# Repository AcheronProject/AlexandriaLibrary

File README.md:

# The Acheron Alexandria Library 

## Introduction

The Alexandria Library is a group of libraries aimed at electronic design; most libraries focus on KiCAD footprints, but some also contain KiCAD symbol libraries, some contain graphics and some contain STEP/3D model files.

## List of libraries:

### General use

- [**Acheron Symbols**](https://github.com/AcheronProject/acheron_Symbols): KiCAD symbol library;
- [**Acheron Components**](https://github.com/AcheronProject/acheron_Symbols): KiCAD footprint library for general components like integrated circuits, resistors, capacitors, LEDs, inductors, fuses *et cetera*;
- [**Acheron Hardware**](https://github.com/AcheronProject/acheron_Hardware.pretty): KiCAD footprint library for overall interaction hardware like standoffs, encoders, featherboards (Pro Micro, Blue Pill, Black Pill *et cetera*), buttons, battery holders, mounting screws;
- [**Acheron Graphics**](https://github.com/AcheronProject/acheron_Graphics.pretty): KiCAD footprint library for logos, flags, pretty graphics;
- [**Acheron 3D**](https://github.com/AcheronProject/acheron_3D): repository of 3D models used by the footprint libraries;

### Keyboard switch footprints

The libraries listed below are KiCAD footprint libraries for mechanical keyboard switches:

- [**Acheron MX**](https://github.com/AcheronProject/acheron_MX.pretty): exclusive support for MX-type switches;
- [**Acheron MX "Soldermask"**](https://github.com/AcheronProject/acheron_MX_soldermask.pretty): exclusive support for MX-type switches with the frontal pads covered in soldermask, hiding the pads in the front while exposing them on the back for soldering, for aesthetic purposes;
- [**Acheron MXH**](https://github.com/AcheronProject/acheron_MXH.pretty): exclusive support for MX-type switches using Kailh "hotswap" sockets;
- [**Acheron MXH "Metal Rings"**](https://github.com/AcheronProject/acheron_MXH_metalrings.pretty): exclusive support for MX-type switches using Kailh "hotswap" sockets with metallic rings around the switch contacts for aesthetic effect;
- [**Acheron MXA**](https://github.com/AcheronProject/acheron_MXA.pretty): hybrid MX-ALPS footprints;
- [**Acheron EC**](https://github.com/AcheronProject/acheron_EC.pretty): exclusive support for electrocapacitive ("Topre-style") switches;

### Macros, makefiles
- [**Acheron Setup**](https://github.com/AcheronProject/AcheronSetup): makefiles and bash scripts to automate some of the work needed to use and maintain a project based on the Acheron Library

### LTSPICE

- [**Acheron LTSPICE**](https://github.com/AcheronProject/acheron_ltspice): symbols and models for the LTSpice simulation software
- [**LT2PY**](https://github.com/Gondolindrim/lt2py): Python tool that converts data plots taken from LTSpice into Python plots, allowing to manipulate and edit the graphs

## Miscellaneous
- [**Acheron Ruler**](https://github.com/AcheronProject/AcheronRuler): in true greek geometry fashion, a ruler featuring both milimeter and inch measurements with electronic components footprints on the back;

## Showing support

Designs using the Alexandria Library into their composition can show support through the KiCAD footprints in the ``./alexandria_kicad_logos'' repository.

## Licensing

Each component of the Alexandria Library is subject to its own licensing and thorough reading is highly advised. This repository itself is licensed under a BSD-3 clause.

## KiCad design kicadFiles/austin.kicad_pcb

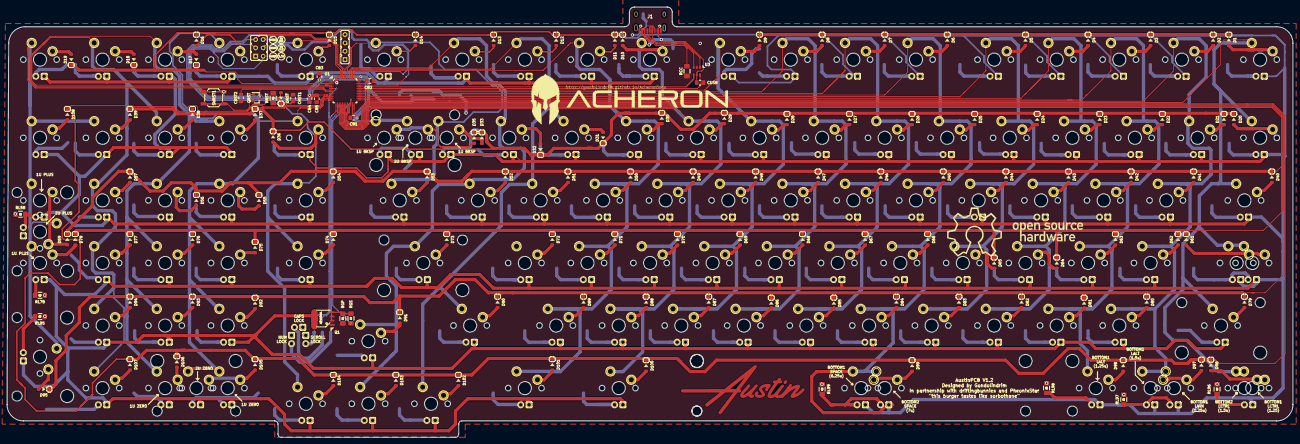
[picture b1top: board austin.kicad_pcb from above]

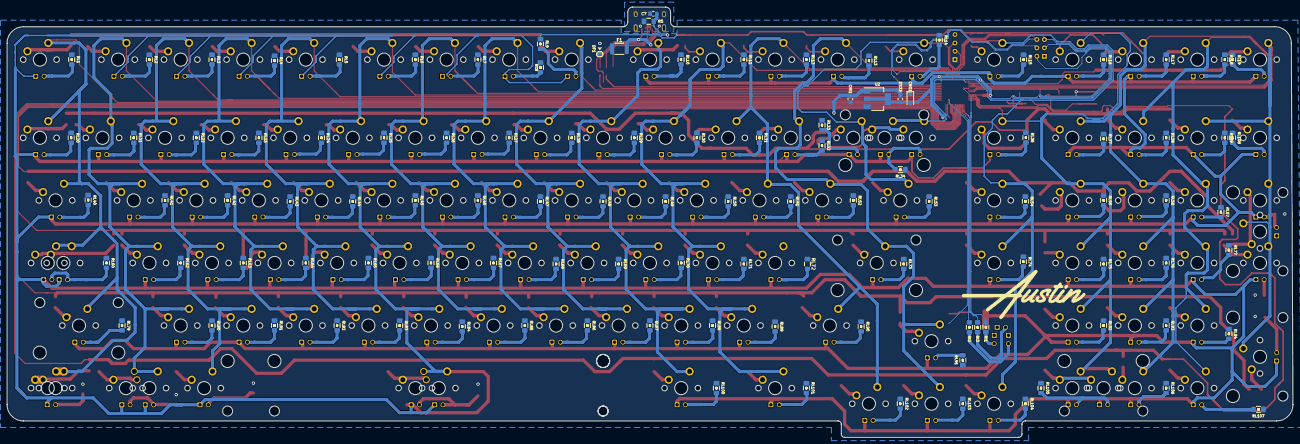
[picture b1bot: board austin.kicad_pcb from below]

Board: 2 copper layers, 391.5 x 131.0 mm, 472 parts (110 on the bottom side), 261 nets.

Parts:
C7: 4.7n; C_0805_2012Metric_Pad1.15x1.40mm_HandSolder
CB1, CB2, CB3, CB4: 100n; C_0805_2012Metric_Pad1.15x1.40mm_HandSolder
CB5: 10u; C_0805_2012Metric_Pad1.15x1.40mm_HandSolder
CRI1: 100n; C_0805_2012Metric_Pad1.15x1.40mm_HandSolder
CRO1: 100n; C_0805_2012Metric_Pad1.15x1.40mm_HandSolder
CRST1: 10u; C_0805_2012Metric_Pad1.15x1.40mm_HandSolder
CRST2: 4.7n; C_0805_2012Metric_Pad1.15x1.40mm_HandSolder
CUSB: 4.7n; C_0805_2012Metric_Pad1.15x1.40mm_HandSolder
D1, D2, D3, D4, D5, D6, D7, D8, D9, D10, D11, D12, D13, D14, D15, D16, D17, D18, D19, D20, D21, D22, D23, D24, D25, D26, D27, D28, D29, D30, D31, D32, D33, D35, D36, D37, D38, D39, D40, D41, D42, D43, D44, D45, D46, D47, D48, D49, D50, D51, D52, D53, D54, D55, D56, D57, D59, D61, D62, D63, D64, D65, D66, D67, D68, D69, D70, D71, D72, D73, D74, D75, D76, D77, D78, D79, D80, D81, D82, D83, D84, D85, D86, D87, D88, D89, D90, D91, D92, D93, D94, D95, D96, D97, D98, D99, D100, D101, D102, D103, D104, D105, D106, D107, D108: 1N4148; D_SOD-123
DF1: RB060M-60TR; D_SOD-123
DRST: 1N4148; D_SOD-123
DS33: 1N4007; D_SOD-123F
F1: 1A; Fuse_1812_4532Metric_Pad1.30x3.40mm_HandSolder
J1: TYPE-C-31-M12_13; TYPE-C-31-M-12
J2: Conn_01x04_Male; 4pinHeader
J5: Conn_01x06_Male; 6pinHeader
L1: Logo; austinLogo_16x40_Plated
L1#2: Logo; austinLogoSmall
L2: LogoBack; acheronLongExtended
L3: OSHLogo; osh-logoExtended
LED1, LED2, LED3, LED4, LED5, LED6, LED7, LED8, LED9, LED10, LED11, LED12, LED13, LED14, LED15, LED16, LED17, LED18, LED19, LED20, LED21, LED22, LED23, LED24, LED25, LED26, LED27, LED28, LED29, LED30, LED31, LED32, LED33, LED34, LED35, LED36, LED37, LED38, LED39, LED40, LED41, LED42, LED43, LED44, LED45, LED46, LED47, LED48, LED49, LED50, LED51, LED52, LED53, LED54, LED55, LED56, LED57, LED58, LED59, LED60, LED61, LED62, LED63, LED64, LED65, LED66, LED67, LED68, LED69, LED70, LED71, LED72, LED73, LED74, LED75, LED76, LED77, LED78, LED79, LED80, LED81, LED82, LED83, LED84, LED85, LED86, LED87, LED88, LED89, LED90, LED91, LED92, LED93, LED94, LED95, LED97, LED98, LED99, LED100, LED101, LED102, LED103, LED104, LED105, LED106, LED107, LED108, LED109, LED110, LED111, LED112: LED; thtLED
LEDCAPS1: LED; thtLED
LEDNUM1: LED; thtLED
LEDSCRL1: LED; thtLED
Q1: AO4406AL
QRST: DTC123J; SOT-23
R5: 1M; R_1206_3216Metric_Pad1.42x1.75mm_HandSolder
RCC: 5.1k; R_1206_3216Metric_Pad1.42x1.75mm_HandSolder
RGP: 10k; R_1026
RGS: 100; R_1026
RI1, RI2, RI3: 360; R_1026
RL1, RL2, RL3, RL4, RL5, RL6, RL7, RL8, RL9, RL10, RL11, RL12, RL13, RL14, RL15, RL16, RL17, RL18, RL19, RL20, RL21, RL22, RL23, RL24, RL25, RL26, RL27, RL28, RL29, RL30, RL31, RL32, RL33, RL34, RL36, RL37, RL38, RL39, RL40, RL41, RL42, RL43, RL44, RL45, RL46, RL47, RL48, RL49, RL50, RL51, RL52, RL53, RL54, RL55, RL56, RL57, RL58, RL60, RL62, RL63, RL64, RL65, RL66, RL67, RL68, RL69, RL70, RL71, RL73, RL74, RL75, RL76, RL77, RL78, RL79, RL80, RL81, RL82, RL83, RL84, RL85, RL86, RL87, RL88, RL89, RL90, RL91, RL92, RL93, RL94, RL95, RL96, RL97, RL98, RL99, RL100, RL101, RL102, RL103, RL104, RL105, RL106, RL107, RL108: 360; R_1026
RL72: 360; R_1206_3216Metric_Pad1.42x1.75mm_HandSolder
RRST: 100k; R_1026
SW1, SW2, SW3, SW4, SW5, SW6, SW7, SW8, SW9, SW10, SW11, SW12, SW13, SW14, SW15, SW16, SW17, SW18, SW19, SW20, SW21, SW22, SW23, SW24, SW25, SW26, SW27, SW28, SW29, SW30, SW31, SW32, SW33, SW35, SW36, SW37, SW38, SW39, SW41, SW42, SW43, SW44, SW45, SW46, SW47, SW48, SW49, SW50, SW51, SW52, SW54, SW55, SW56, SW57, SW58, SW62, SW63, SW64, SW65, SW66, SW67, SW68, SW69, SW70, SW71, SW72, SW74, SW75, SW76, SW77, SW78, SW80, SW81, SW82, SW83, SW84, SW85, SW86, SW87, SW88, SW89, SW91, SW92, SW93, SW94, SW102, SW103, SW104, SW105, SW106, SW107, SW108: MXSwitch; MX100
SW34: MXSwitch; MX200
SW40, SW53, SW100, SW101, SW109, SW110: MXSwitch; MX150
SW59, SW95, SW112: MXSwitch; MX200R
SW60, SW90: MXSwitch; MX175
SW61, SW96, SW97, SW98: MXSwitch; MX125
SW73, SW79: MXSwitch; MX225
SW99: MXSwitch; MX625R
SW111: MXSwitch; MX700R
SWRST1: SW_Push; smdPushBtn
U1: STM32F072_LQFP48; LQFP-48_7x7mm_P0.5mm
U2: TLV1117-33; SOT-223-3_TabPin2
U3: USBLC6-2SC6; SOT-23-6

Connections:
3.3V: CB1.1, CB2.1, CB3.1, CB4.1, CB5.1, CRO1.2, DS33.2, J5.6, SWRST1.1, U1.1, U1.9, U1.24, U1.36, U1.48, U2.2
5V: CRI1.2, DF1.1, DS33.1, F1.1, J2.1, RL1.1, RL2.1, RL3.1, RL4.1, RL5.1, RL6.1, RL7.1, RL8.1, RL9.1, RL10.1, RL11.1, RL12.1, RL13.1, RL14.1, RL15.1, RL16.1, RL17.1, RL18.1, RL19.1, RL20.1, RL21.1, RL22.1, RL23.1, RL24.1, RL25.1, RL26.1, RL27.1, RL28.1, RL29.1, RL30.1, RL31.1, RL32.1, RL33.1, RL34.1, RL36.1, RL37.1, RL38.1, RL39.1, RL40.1, RL41.1, RL42.1, RL43.1, RL44.1, RL45.1, RL46.1, RL47.1, RL48.1, RL49.1, RL50.1, RL51.1, RL52.1, RL53.1, RL54.1, RL55.1, RL56.1, RL57.1, RL58.1, RL60.1, RL62.1, RL63.1, RL64.1, RL65.1, RL66.1, RL67.1, RL68.1, RL69.1, RL70.1, RL71.1, RL72.1, RL73.1, RL74.1, RL75.1, RL76.1, RL77.1, RL78.1, RL79.1, RL80.1, RL81.1, RL82.1, RL83.1, RL84.1, RL85.1, RL86.1, RL87.1, RL88.1, RL89.1, RL90.1, RL91.1, RL92.1, RL93.1, RL94.1, RL95.1, RL96.1, RL97.1, RL98.1, RL99.1, RL100.1, RL101.1, RL102.1, RL103.1, RL104.1, RL105.1, RL106.1, RL107.1, RL108.1, U2.3
/LEDK: LED1.K, LED2.K, LED3.K, LED4.K, LED5.K, LED6.K, LED7.K, LED8.K, LED9.K, LED10.K, LED11.K, LED12.K, LED13.K, LED14.K, LED15.K, LED16.K, LED17.K, LED18.K, LED19.K, LED20.K, LED21.K, LED22.K, LED23.K, LED24.K, LED25.K, LED26.K, LED27.K, LED28.K, LED29.K, LED30.K, LED31.K, LED32.K, LED33.K, LED34.K, LED35.K, LED36.K, LED37.K, LED38.K, LED39.K, LED40.K, LED41.K, LED42.K, LED43.K, LED44.K, LED45.K, LED46.K, LED47.K, LED48.K, LED49.K, LED50.K, LED51.K, LED52.K, LED53.K, LED54.K, LED55.K, LED56.K, LED57.K, LED58.K, LED60.K, LED61.K, LED62.K, LED63.K, LED64.K, LED65.K, LED66.K, LED67.K, LED68.K, LED69.K, LED70.K, LED71.K, LED72.K, LED73.K, LED74.K, LED75.K, LED76.K, LED77.K, LED78.K, LED79.K, LED80.K, LED81.K, LED82.K, LED83.K, LED84.K, LED85.K, LED86.K, LED87.K, LED88.K, LED89.K, LED90.K, LED91.K, LED92.K, LED93.K, LED94.K, LED95.K, LED97.K, LED98.K, LED99.K, LED100.K, LED101.K, LED102.K, LED103.K, LED104.K, LED105.K, LED106.K, LED107.K, LED108.K, LED109.K, LED110.K, LED111.K, LED112.K, Q1.D
BOOT0: CRST1.2, DRST.1, J5.3, RRST.1, U1.44
CAPSLCK: RI3.1, U1.13
Col1: SW1.1, SW20.1, SW40.1, SW60.1, SW61.1, SW79.1, SW96.1, SW109.1, U1.20
Col2: SW2.1, SW21.1, SW41.1, SW62.1, SW80.1, SW97.1, SW110.1, U1.21
Col3: SW3.1, SW22.1, SW42.1, SW63.1, SW81.1, SW98.1, U1.25
Col4: SW4.1, SW23.1, SW43.1, SW64.1, SW82.1, U1.26
Col5: SW5.1, SW24.1, SW44.1, SW65.1, SW83.1, U1.27
Col6: SW6.1, SW25.1, SW45.1, SW66.1, SW84.1, SW99.1, SW111.1, U1.28
Col7: SW7.1, SW26.1, SW46.1, SW67.1, SW85.1, U1.29
Col8: SW8.1, SW27.1, SW47.1, SW68.1, SW86.1, U1.30
Col9: SW9.1, SW28.1, SW48.1, SW69.1, SW87.1, U1.31
Col10: SW10.1, SW29.1, SW49.1, SW70.1, SW88.1, SW100.1, U1.15
Col11: SW11.1, SW30.1, SW50.1, SW71.1, SW89.1, SW101.1, U1.38
Col12: SW12.1, SW31.1, SW51.1, SW90.1, SW102.1, U1.39
Col13: SW13.1, SW32.1, SW52.1, SW73.1, SW91.1, SW103.1, U1.40
Col14: SW14.1, SW33.1, SW53.1, U1.41
Col15: SW15.1, SW34.1, SW35.1, SW54.1, SW74.1, SW104.1, U1.45
Col16: SW16.1, SW36.1, SW55.1, SW75.1, SW92.1, SW105.1, SW112.1, U1.12
Col17: SW17.1, SW37.1, SW56.1, SW76.1, SW93.1, SW106.1, U1.4
Col18: SW18.1, SW38.1, SW57.1, SW77.1, SW94.1, SW107.1, U1.3
Col19: SW19.1, SW39.1, SW58.1, SW59.1, SW78.1, SW95.1, SW108.1, U1.6
D+: U1.33, U3.4
D+Bus: J1.A6, J1.B6, U3.3
D-: U1.32, U3.6
D-Bus: J1.A7, J1.B7, U3.1
GND: C7.1, CB1.2, CB2.2, CB3.2, CB4.2, CB5.2, CRI1.1, CRO1.1, CRST1.1, CRST2.2, CUSB.1, DF1.2, J1.A1, J1.B1, J2.4, J5.1, LEDCAPS1.K, LEDNUM1.K, LEDSCRL1.K, Q1.S, QRST.2, R5.2, RCC.1, RGP.1, RRST.2, U1.8, U1.23, U1.35, U1.47, U2.1, U3.2
LED_PWM: RGS.2, U1.22
NRST: CRST2.1, J5.2, QRST.3, U1.7
NUMLCK: RI2.1, U1.14
unnamed: C7.2, J1.S, R5.1
unnamed: D1.2, SW1.2
unnamed: D2.2, SW2.2
unnamed: D3.2, SW3.2
unnamed: D4.2, SW4.2
unnamed: D5.2, SW5.2
unnamed: D6.2, SW6.2
unnamed: D7.2, SW7.2
unnamed: D8.2, SW8.2
unnamed: D9.2, SW9.2
unnamed: D10.2, SW10.2
unnamed: D11.2, SW11.2
unnamed: D12.2, SW12.2
unnamed: D13.2, SW13.2
unnamed: D14.2, SW14.2
unnamed: D15.2, SW15.2
unnamed: D16.2, SW16.2
unnamed: D17.2, SW17.2
unnamed: D18.2, SW18.2
unnamed: D19.2, SW19.2
unnamed: D20.2, SW20.2
unnamed: D21.2, SW21.2
unnamed: D22.2, SW22.2
unnamed: D23.2, SW23.2
unnamed: D24.2, SW24.2
unnamed: D25.2, SW25.2
unnamed: D26.2, SW26.2
unnamed: D27.2, SW27.2
unnamed: D28.2, SW28.2
unnamed: D29.2, SW29.2
unnamed: D30.2, SW30.2
unnamed: D31.2, SW31.2
unnamed: D32.2, SW32.2
unnamed: D33.2, SW33.2
unnamed: D35.2, SW34.2, SW35.2
unnamed: D36.2, SW36.2
unnamed: D37.2, SW37.2
unnamed: D38.2, SW38.2
unnamed: D39.2, SW39.2
unnamed: D40.2, SW40.2
unnamed: D41.2, SW41.2
unnamed: D42.2, SW42.2
unnamed: D43.2, SW43.2
unnamed: D44.2, SW44.2
unnamed: D45.2, SW45.2
unnamed: D46.2, SW46.2
unnamed: D47.2, SW47.2
unnamed: D48.2, SW48.2
unnamed: D49.2, SW49.2
unnamed: D50.2, SW50.2
unnamed: D51.2, SW51.2
unnamed: D52.2, SW52.2
unnamed: D53.2, SW53.2
unnamed: D54.2, SW54.2
unnamed: D55.2, SW55.2
unnamed: D56.2, SW56.2
unnamed: D57.2, SW57.2
unnamed: D59.2, SW58.2, SW59.2
unnamed: D61.2, SW60.2, SW61.2
unnamed: D62.2, SW62.2
unnamed: D63.2, SW63.2
unnamed: D64.2, SW64.2
unnamed: D65.2, SW65.2
unnamed: D66.2, SW66.2
unnamed: D67.2, SW67.2
unnamed: D68.2, SW68.2
unnamed: D69.2, SW69.2
unnamed: D70.2, SW70.2
unnamed: D71.2, SW71.2
unnamed: D72.2, SW72.2
unnamed: D73.2, SW73.2
unnamed: D74.2, SW74.2
unnamed: D75.2, SW75.2
unnamed: D76.2, SW76.2
unnamed: D77.2, SW77.2
unnamed: D78.2, SW78.2
unnamed: D79.2, SW79.2
unnamed: D80.2, SW80.2
unnamed: D81.2, SW81.2
unnamed: D82.2, SW82.2
unnamed: D83.2, SW83.2
unnamed: D84.2, SW84.2
unnamed: D85.2, SW85.2
unnamed: D86.2, SW86.2
unnamed: D87.2, SW87.2
unnamed: D88.2, SW88.2
unnamed: D89.2, SW89.2
unnamed: D90.2, SW90.2
unnamed: D91.2, SW91.2
unnamed: D92.2, SW92.2
unnamed: D93.2, SW93.2
unnamed: D94.2, SW94.2
unnamed: D95.2, SW95.2
unnamed: D96.2, SW96.2, SW109.2
unnamed: D97.2, SW97.2, SW110.2
unnamed: D98.2, SW98.2
unnamed: D99.2, SW99.2, SW111.2
unnamed: D100.2, SW100.2
unnamed: D101.2, SW101.2
unnamed: D102.2, SW102.2
unnamed: D103.2, SW103.2
unnamed: D104.2, SW104.2
unnamed: D105.2, SW105.2, SW112.2
unnamed: D106.2, SW106.2
unnamed: D107.2, SW107.2
unnamed: D108.2, SW108.2
unnamed: DRST.2, QRST.1, SWRST1.2
unnamed: J1.A5, J1.B5, RCC.2
unnamed: LED1.A, RL1.2
unnamed: LED2.A, RL2.2
unnamed: LED3.A, RL3.2
unnamed: LED4.A, RL4.2
unnamed: LED5.A, RL5.2
unnamed: LED6.A, RL6.2
unnamed: LED7.A, RL7.2
unnamed: LED8.A, RL8.2
unnamed: LED9.A, RL9.2
unnamed: LED10.A, RL10.2
unnamed: LED11.A, RL11.2
unnamed: LED12.A, RL12.2
unnamed: LED13.A, RL13.2
unnamed: LED14.A, RL14.2
unnamed: LED15.A, RL15.2
unnamed: LED16.A, RL16.2
unnamed: LED17.A, RL17.2
unnamed: LED18.A, RL18.2
unnamed: LED19.A, RL19.2
unnamed: LED20.A, RL20.2
unnamed: LED21.A, RL21.2
unnamed: LED22.A, RL22.2
unnamed: LED23.A, RL23.2
unnamed: LED24.A, RL24.2
unnamed: LED25.A, RL25.2
unnamed: LED26.A, RL26.2
unnamed: LED27.A, RL27.2
unnamed: LED28.A, RL28.2
unnamed: LED29.A, RL29.2
unnamed: LED30.A, RL30.2
unnamed: LED31.A, RL31.2
unnamed: LED32.A, RL32.2
unnamed: LED33.A, RL33.2
unnamed: LED34.A, LED35.A, RL34.2
unnamed: LED36.A, RL36.2
unnamed: LED37.A, RL37.2
unnamed: LED38.A, RL38.2
unnamed: LED39.A, RL39.2
unnamed: LED40.A, RL40.2
unnamed: LED41.A, RL41.2
unnamed: LED42.A, RL42.2
unnamed: LED43.A, RL43.2
unnamed: LED44.A, RL44.2
unnamed: LED45.A, RL45.2
unnamed: LED46.A, RL46.2
unnamed: LED47.A, RL47.2
unnamed: LED48.A, RL48.2
unnamed: LED49.A, RL49.2
unnamed: LED50.A, RL50.2
unnamed: LED51.A, RL51.2
unnamed: LED52.A, RL52.2
unnamed: LED53.A, RL53.2
unnamed: LED54.A, RL54.2
unnamed: LED55.A, RL55.2
unnamed: LED56.A, RL56.2
unnamed: LED57.A, RL57.2
unnamed: LED58.A, LED59.A, RL58.2
unnamed: LED60.A, LED61.A, RL60.2
unnamed: LED62.A, RL62.2
unnamed: LED63.A, RL63.2
unnamed: LED64.A, RL64.2
unnamed: LED65.A, RL65.2
unnamed: LED66.A, RL66.2
unnamed: LED67.A, RL67.2
unnamed: LED68.A, RL68.2
unnamed: LED69.A, RL69.2
unnamed: LED70.A, RL70.2
unnamed: LED71.A, RL71.2
unnamed: LED72.A, RL72.2
unnamed: LED73.A, RL73.2
unnamed: LED74.A, RL74.2
unnamed: LED75.A, RL75.2
unnamed: LED76.A, RL76.2
unnamed: LED77.A, RL77.2
unnamed: LED78.A, RL78.2
unnamed: LED79.A, RL79.2
unnamed: LED80.A, RL80.2
unnamed: LED81.A, RL81.2
unnamed: LED82.A, RL82.2
unnamed: LED83.A, RL83.2
unnamed: LED84.A, RL84.2
unnamed: LED85.A, RL85.2
unnamed: LED86.A, RL86.2
unnamed: LED87.A, RL87.2
unnamed: LED88.A, RL88.2
unnamed: LED89.A, RL89.2
unnamed: LED90.A, RL90.2
unnamed: LED91.A, RL91.2
unnamed: LED92.A, RL92.2
unnamed: LED93.A, RL93.2
unnamed: LED94.A, RL94.2
unnamed: LED95.A, RL95.2
unnamed: LED98.A, RL98.2
unnamed: LED100.A, RL100.2
unnamed: LED101.A, RL101.2
unnamed: LED102.A, RL102.2
unnamed: LED103.A, RL103.2
unnamed: LED104.A, RL104.2
unnamed: LED105.A, LED112.A, RL105.2
unnamed: LED106.A, RL106.2
unnamed: LED107.A, RL107.2
unnamed: LED108.A, RL108.2
unnamed: LED109.A, RL96.2
unnamed: LED97.A, LED110.A, RL97.2
unnamed: LED99.A, LED111.A, RL99.2
unnamed: LEDCAPS1.A, RI3.2
unnamed: LEDNUM1.A, RI2.2
unnamed: LEDSCRL1.A, RI1.2
unnamed: Q1.G, RGP.2, RGS.1
Row1: D1.1, D2.1, D3.1, D4.1, D5.1, D6.1, D7.1, D8.1, D9.1, D10.1, D11.1, D12.1, D13.1, D14.1, D15.1, D16.1, D17.1, D18.1, D19.1, U1.2
Row2: D20.1, D21.1, D22.1, D23.1, D24.1, D25.1, D26.1, D27.1, D28.1, D29.1, D30.1, D31.1, D32.1, D33.1, D35.1, D36.1, D37.1, D38.1, D39.1, U1.11
Row3: D40.1, D41.1, D42.1, D43.1, D44.1, D45.1, D46.1, D47.1, D48.1, D49.1, D50.1, D51.1, D52.1, D53.1, D54.1, D55.1, D56.1, D57.1, D59.1, U1.16
Row4: D61.1, D62.1, D63.1, D64.1, D65.1, D66.1, D67.1, D68.1, D69.1, D70.1, D71.1, D72.1, D73.1, D74.1, D75.1, D76.1, D77.1, D78.1, U1.17
Row5: D79.1, D80.1, D81.1, D82.1, D83.1, D84.1, D85.1, D86.1, D87.1, D88.1, D89.1, D90.1, D91.1, D92.1, D93.1, D94.1, D95.1, U1.18
Row6: D96.1, D97.1, D98.1, D99.1, D100.1, D101.1, D102.1, D103.1, D104.1, D105.1, D106.1, D107.1, D108.1, U1.19
SCL: J2.3, U1.42
SCRLLCK: RI1.1, U1.5
SDA: J2.2, U1.43
SWCLK: J5.5, U1.37
SWDIO: J5.4, U1.34
VBUS: CUSB.2, F1.2, J1.A4, J1.B4, U3.5

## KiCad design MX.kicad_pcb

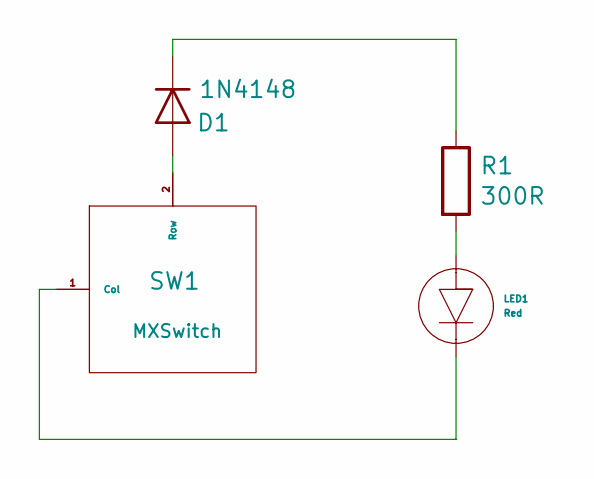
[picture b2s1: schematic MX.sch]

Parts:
D1: 1N4148; thtDiode
LED1: Red; thtLED
R1: 300R; R_Axial_DIN0204_L3.6mm_D1.6mm_P5.08mm_Horizontal
SW1: MXSwitch; MX100

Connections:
unnamed: D1.1 (K), R1.1
unnamed: D1.2 (A), SW1.2 (Row)
unnamed: LED1.A, R1.2
unnamed: LED1.K, SW1.1 (Col)

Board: 2 copper layers, 4 parts (0 on the bottom side), 4 nets, no tracks yet.

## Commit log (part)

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2018-11-25 Fixed names
2018-11-27 Upated MX700H and MX700HR
2018-11-27 Added support for THT LEDs
2018-11-27 Improved silkscreen markings, LED footprints and added diode footprint
2018-11-28 Renamed datasheets
2018-11-28 Fixed the offset in the 3D model of thtDiode
2018-11-28 Dimension markings in the MX100 were put on the Comments layer
2018-11-29 Reversed switch contact numbering
2018-11-29 Organized folders
2018-12-01 Fixed courtyard measures
2018-12-15 Fixed USB connector
2018-12-17 Added AO4406AL NMOS footprint and symbol
2019-01-22 Added MX100HT footprint
2019-02-14 Added footprints for crystal, push button, switch plate slots
2019-02-21 Fixed slot100 dimension issue
2019-02-28 Removed old files
2019-02-28 Corrected README
2019-03-11 Added license file
2019-03-13 Added JST connector footprint. Plate switch slots were revamped.
2019-03-13 Revamped README.
2019-03-25 [Features] Added new components, datasheets and footprints
2019-06-08 [Update] New 3D files
2019-06-12 [Pre-release] V1.0 pre-release
2019-06-12 [Update] Added single centroid file
2019-06-13 [Update] Version 1.1
2019-06-20 [Update] V2.0 release
2019-06-20 [Update] V1.2: plated logo, new easter egg
2019-06-21 V2.1 tagged
2019-06-30 Tagged pre-Alpha version and released gerbers
2019-07-05 [Update] Updated all existing footprints
2019-07-05 [Feature] Added 6U footprints for MX. MX series is complete.
2019-07-07 [Update,Feature] Renamed footprints for clearance, added symbol for ATMEGA32U4
2019-07-09 [Feature] Added ATMEGA32U4 symbol
2019-07-09 [Fix] Fixed pin 39 offset
2019-07-09 [Fix] ATMEGA32U4 footprint pin 33 was marked PD5 when it should be PE2/~HWB~
2019-07-09 [Update] Removed halfSideHole footprint, as the sideHole one is redundant
2019-07-09 [Update] Updated documentation of the M12 Type-C connector and SMD push button. Added 3D model to the USB MiniB XM7D
2019-07-10 [Feature] Added Hirose 5S8 footprint with 3D model
2019-07-10 [Fix] Removed the linking traces on the D-7.62mm-SOD-123 footprint
2019-07-12 [Feature] Added ISO enter
2019-07-13 [Update] Rotated ISO Enter switch, added multi-pin to AO4406AL symbol
2019-07-14 [Update] Updated STM32F072-LQFP48 symbol to squared model
2019-07-23 [Update] Added better documentation on F.Fab and B.Fab layers on some footprints
2019-07-23 [Feature] Added SMD 1206 LED footprint
2019-07-24 [Update] Re-assigned LED pins. Removed I2C pin header breakouts.
2019-07-24 [Update] Cleaned up fab layers, updated gerber
2019-07-24 [Update] Renamed C7 and R5 to RSH1 and CSH1, updated gerbers
2019-07-28 [Update] Added SOP-8 footprint
2019-07-29 [Update] Refreshed gerbers and pos file for production just in case
2019-07-29 [Feature] Added SOP-8 and RGB E6C12 RGB LED
2019-07-30 [Update] Finished re-routing the connector area, ran DRC
2019-07-31 [Update,Feature] Renamed mounting holes for better understanding; added side mouting hole and reversed oval hole
2019-07-31 [Update] Refreshed gerbers and position file
2019-08-02 [Update,Feature] Added 3D model for RGB LED
2019-08-02 [Update] Added Acheron Short logo
2019-08-12 Changed SOD123 and MX; new 3D model for 6028 LED
    - The silkscreen around the cathode pad of the D_SOD-123 footprint turned out not so great in an actual PCB (used JLCPCB for the prototyping). Those silkscreen became faded and really thin, too close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
    Footprints affected:
    acheron_Components.pretty/D_SOD-123.kicad_mod
    - The MX footprints had silkscreen rings around the pads, which turned out not so great, so those silkscreen markings were removed. No further modifications were done.
    Footprints affected:
    acheron_MX.pretty/MX100.kicad_mod
2019-08-12 Removed inkscape temporary crash file
2019-08-12 Added README for graphics/
2019-08-12 Added bigger short Acheron logo
    - A new 15x21mm Acheron Short logo was added; both silkscreen and plated versions are there.
2019-08-16 Renamed osh-logo folder, added warning sign
    - A warning sign and a shock sign footprints were added;
    - The osh-logo folder was renamed to acheron_Graphics as it contained not only the OSH logo, but also US and BR flags, and now the warning sign and shock sign warnings.
2019-08-16 Added Acheron logo for READMEs
2019-08-21 Add new ATMEGA32U4-QFN symbol
    - Added a new ATMEGA32U4-QFN symbol. This is needed because the original symbold didnt have pin 45, which represents the thermal pad of the QFM package. The new QFN symbol is the same than the old on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
2019-08-26 Add STM32F103 symbol
2019-08-26 Add UQFN-48 footprint
2019-08-26 Add STM32F103-UQFN symbol
2019-09-09 Add MX_SolderMask footprints
2019-09-15 Add RCC2
    - In version pre-Alpha, the RCC pins were wrongly connected with a single RCC resistor. This is not the right way to implement USBC 3.0 connection; in actuality, each of the two pins should have a si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
    - The RCC resistors also had their package changed; before they were 1206, and now are 0402. This is meant to save space around the connector area.
2019-09-15 Add RF1; change CSI1 to CF1 and to 10uF
    - The CSI1 capacitor was changed to 10uF, a more stable value that should offer more voltage regulator for the LDO;
    - CSI1 was re-named CF1 for Capacitor-Fuse;
    - In order not to leave CF1 charged when the PCB is not powered on, a resistor RF1 was added to discharge CF1 after turn off.
2019-09-15 Implement schematic changes to PCB
2019-09-15 Run DRC and solve issues
2019-09-15 Edit gitignore
2019-09-20 Improve MX_SolderMask footprints
    - The MX_SolderMask footprints were improved. The buried pads were too thin; they were made thicker to improve sustenance and quality of the footprint.
2019-09-21 [Update] TYPEC connector redone
    - In some commits ago, I made so that this connector had a thicker
    plated pad on the back of the connector, since I thought the connector
    was soldered from the backside. This is not the case; the connector is
    actually soldered from the front side, through hot air and solder paste
    soldering.
2019-09-21 Improve Acheron Project long logo
    - The AcheronProject long logo features the AcheronDocs website. The
    problem is that the inscription was too small and looked blurry in a real
    silkscreen marking. Since I didn't want to make it bigger and overshadow
    the Acheron logo, I outright removed the website inscription from it.
2019-09-23 Fix: back-only oval mounting hole
2019-09-23 Fix: Dwgs.User measurement issue with MX150H
2019-09-24 Fix: dimension problem of MX125H footprint
2019-09-24 Feature: 1x7 pin header
2019-09-27 Fix: back-only oval hole
    - There was an issue with the back-only oval hole footprint, in which
    the inside of the hole would still be metallized, possibly causing
    unintended short circuits. This has been fixed and how the hole plating
    is on the pad only.
2019-09-29 Update: south facing stabs, indicators silkscreen
    - Due to a recommendation by anthony001, the spacebar and numpad 0
    stabilizers were made south-facing due to that being the default
    configuration.
    - Also, the indicator LEDs were marked SCROLL/NUM/CAPS LOCK in the
    silkscreen. This does not make sense as the order of the LEDs is
    customizable and programmable to the liking of the user. Now the
2019-09-30 Update: corrected pads on SMD RGB LED footprint
    - The LED_RGB_SMD_6028 footprint was really crude in the sense that it
    was developed with pads that overlapped the center hole. This caused
    KiCad's DRC to fire up four errors for each unit used in the PCB; in the
    TheKeenLadies PCB, this amounted to almos 2000 errors. The pads were now
    fine-tunes to the exact shape of the center hole, with a 6 mil spacing
    between them.
2019-10-09 Add 2016 crystal footprint
2019-10-16 Update 6028 LED footprint
    - The footprint is now marked as an SMD component
2019-10-20 Add ACM2012 and IPC7351 mousebite footprints
2019-10-25 Added SOD-123 bidirectional footprint
2019-11-05 Fix TYPE-C-31-M-12 footprint
    - This footprint had one if its pads with B.SilkS marking which was
    removed.
2019-11-12 Rename R_1026 footprint to R_1206
2019-11-24 Add plate cutouts to switch footprints
    - The MX series of switches had plate cutouts added to the Eco1.User layer, so that a plate DXF can be output right as the PCB is done. This update is not yet available for MX_SolderMask nor MXA foot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
2019-11-27 Enhance XM7D USB connector footprint to make pads bigger
2019-11-28 amended meta data for hotswap to indicate smd component
2019-11-28 Fix switch alignments
2019-11-28 Remove solder paste layer from XM7D footprint
2019-11-28 Add hot swap ISO footprint
2019-11-29 Added 6-pin AVR ISP footprint
2019-11-30 fix switch orientation
2019-12-13 Added USB connector footprints
2019-12-13 Review D_SOD-123_Bidirectional footprint
2019-12-15 Added MX ISO Enter footprint with LED support
    This footprint is meant to be used so that the PCB can support the ISO enter and per-key LEDs; when a north-facing switch footprint is used, the switch pad will clash with the LED pads. This is gener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
2019-12-18 Solve big pads issue on TYPE-C-M-12 footprint
2019-12-18 Made THT LED footprint have soldermask covered pads on back side
2020-01-04 Add 12 pin header footprint
2020-01-08 Add metadata and footprints
2020-01-15 Add 1x16 and 1x20 pin header footprints
2020-01-15 Moved silkscreen on SOD123 footprint
2020-01-15 Renamed switchSlots to MX_PlateSlots
2020-01-18 Solve mounting hole footprint issue
    The back-only oval mounting hole footprint was made using a mechanical hole and an SMD pad. This would trigger a lot of errors in DRC checks. The footprint was reworked the right way as a single-side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
2020-01-28 Solve courtyard issue in 1x9 header footprint
2020-02-07 Add USON-10 footprint and TPD4E05U06DQAR symbol
2020-03-02 Add shielded rotary encoder symbol
2020-03-03 Add 1x2 pin header
2020-04-03 Add TE 4-pin connectors
2020-04-08 Fix STM32F072 symbol
2020-04-12 Add 1x3 pin header footprint
2020-04-12 Add SM13B footprint
2020-05-04 Added Diodes Inc AP63203WU-7
2020-05-05 Added default footprint for AP63203WU-7
2020-05-08 Added Powered By Acheron Tall 10mm Logos
2020-05-14 Removed originals folder
2020-05-31 Add TYPE-C-31-M-14 footprint and 3D model
2020-06-10 Add shield pad to EC11Ex footprint
2020-06-10 Add WS2812B-Mini footprint and 3D model
2020-06-12 Port symbol library to new kicad_sym format
2020-06-12 Add SOT-262 footprint
2020-06-24 New improved plate cutouts
2020-06-27 Changed license to BSD 2-clause
2020-06-27 Add RKJXT1F42001 footprint
2020-07-02 Fixed MX solderable 600 switch
2020-07-02 New SOT-34 footprints
2020-07-14 Add TXS0101 symbol
2020-07-23 Fix MX footprint plate cutouts for simpler variants
2020-07-25 Added 6-pin viariant of ARM SWD JTAG
2020-07-27 Creatred 1.152mm tooling hole for JLCPCB SMT assembly
    Per https://support.jlcpcb.com/article/92-how-to-add-tooling-holes-for-smt-assembly-order
2020-08-03 Added PEM-KF2-M3-ET
2020-08-03 Renamed PEM-KF2-M3 to point out that it is meant to be soldered in
2020-08-26 Add mounting reliefs SM04B footprint, remove duplicates
2020-08-28 Small schematic changes
2020-08-28 Update AcheronLibrary
2020-08-29 Revamp copper pours, place and wire MCU
2020-09-02 Initial electrocapacitive pad footprint
    - TZARC IS GOD
2020-09-02 New electrocapacitive switch symbol
2020-09-02 New SOT-363 and QFN-16 footprints
2020-09-20 Remove URL from Acheron Readme images
2020-11-09 Add SM14B and SM05B footprints and 3d models
2021-01-23 New 6U footprints
    - The off-center 6U footprints had a small stab marking issue where the lines that mark the stabs were misaligned towards the left
    - Added centered and off-center 6U switches
2021-01-23 Fixed MX300 footprint to have 3U stab wire
2021-02-09 Change 3D model of hotswap sockets to reference
2021-02-09 Make SK6912 silkscreen as 25/25/5 mil sizes
2021-02-10 Added basic 3D model of this part (modeled myself; no license violations here)
2021-03-08 Create USB2_A_Molex_0482580002.kicad_mod
    Made a footprint for a mid-mount USB 2.0 A receptacle here:
    Datasheet:
    https://www.molex.com/pdm_docs/sd/482580002_sd.pdf
    I made the footprint upside down as that's the correct orientation for USB (the connector is "Reverse type", so if you soldered it on the top of the board the USB connector would be upside down)
2021-03-08 Fixed mistake where shield tabs were pin 6 instead of pin 5
    Shield tabs are now pin 5, the same as the other shield pins
2021-03-12 Add LQFP64 and 3225 crystal footprints
2021-08-12 Started porting to Alexandria format
    - Removed all libraries
    - Added Alexandria Logo
    - Renewed README
2021-08-12 Fix README logo
2021-08-12 Added 'powered by' footprints
